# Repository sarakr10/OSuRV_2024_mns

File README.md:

# OSuRV_2024

[Prj table](https://docs.google.com/spreadsheets/d/11ApFMVwyrgWKrQ-Bx30LXNKMNhpXhl4f)

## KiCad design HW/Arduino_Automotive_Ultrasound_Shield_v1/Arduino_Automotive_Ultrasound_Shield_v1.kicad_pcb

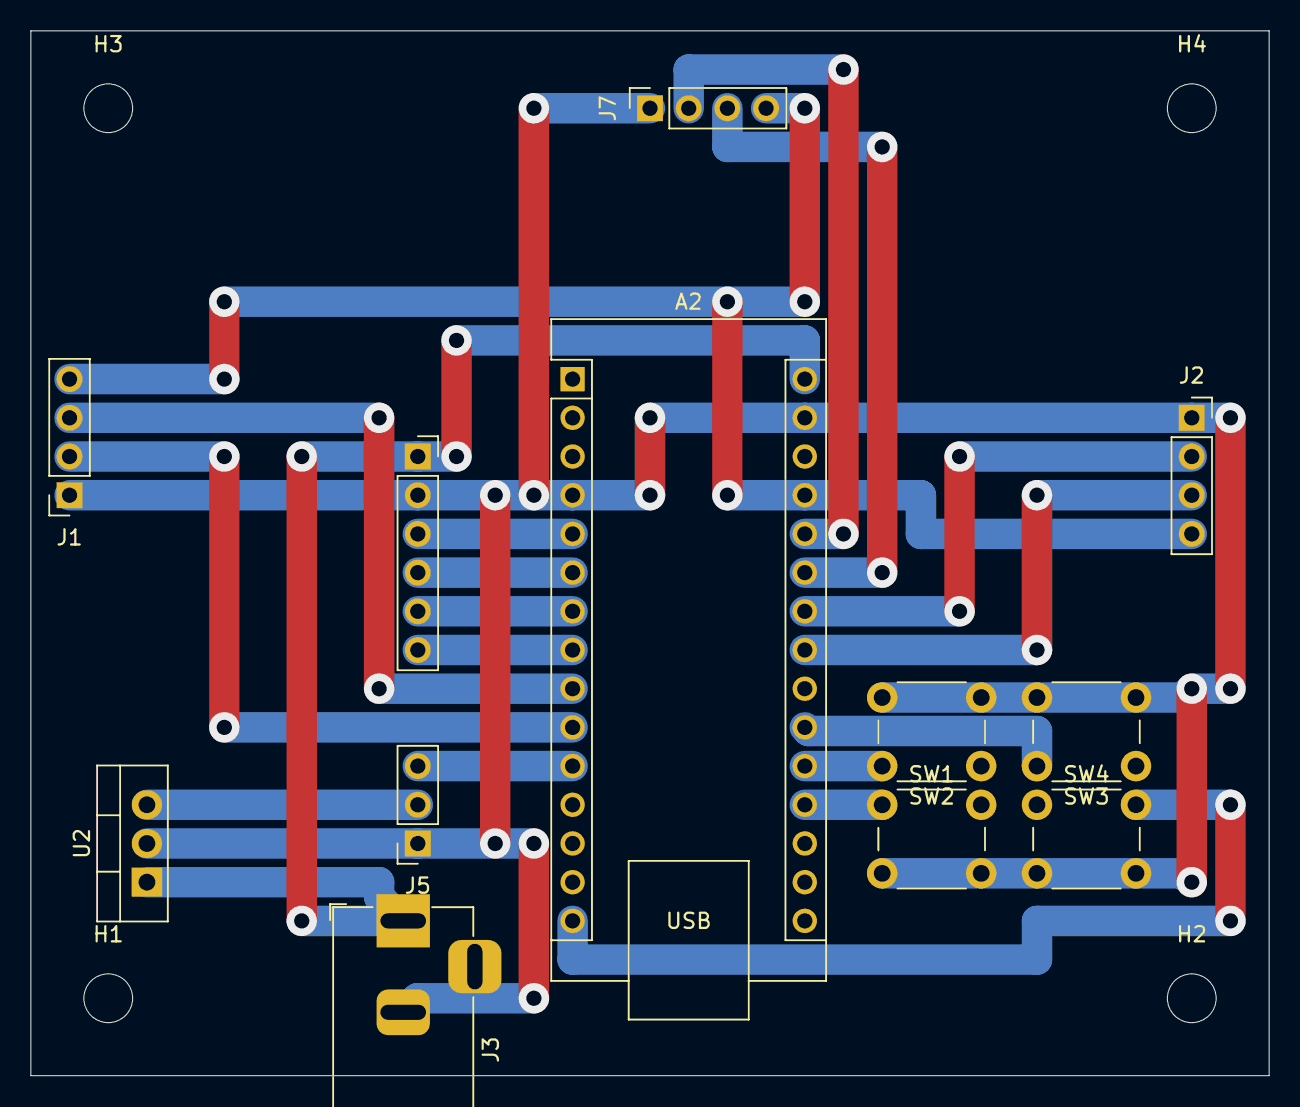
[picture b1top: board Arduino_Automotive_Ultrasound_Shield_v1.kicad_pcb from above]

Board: 2 copper layers, 81.3 x 68.6 mm, 16 parts (0 on the bottom side), 19 nets.

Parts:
A2: Arduino_Nano_Every; Arduino_Nano
H1, H2, H3, H4: M3; MountingHole_3.2mm_M3
J1, J2, J7: 1x4 2.54mm female; PinSocket_1x04_P2.54mm_Vertical
J3: Barrel_Jack_Switch; BarrelJack_Horizontal
J5: 1x3 2.54mm male; PinSocket_1x03_P2.54mm_Vertical
J6: 1x3 2.54mm male; PinSocket_1x06_P2.54mm_Vertical
SW1, SW2, SW3, SW4: SW_Push; SW_PUSH_6mm
U2: LM7805_TO220; TO-220-3_Vertical

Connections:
+5V: A2.27 (+5V), J1.4, J2.4, J7.4
+12V: A2.30 (VIN), J3.1, J6.1, U2.1 (VI)
/BREAK: A2.8 (D5), J6.6
/DIR: A2.7 (D4), J6.5
/ECHO_0: A2.26 (A7), J7.2
/ECHO_1: A2.24 (SCL/A5), J2.2
/ECHO_2: A2.10 (D7), J1.2
/FG: A2.5 (D2), J6.3
/PB0: A2.21 (A2), SW1.1
/PB1: A2.20 (A1), SW2.1
/PB2: A2.19 (A0), SW3.1
/PB3: A2.15 (MISO), SW4.1
/PWM: A2.6 (D3), J6.4
/STEER_PWM: A2.11 (D8), J5.3
/TRIG_0: A2.25 (A6), J7.3
/TRIG_1: A2.23 (SDA/A4), J2.3
/TRIG_2: A2.9 (D6), J1.3
GND: A2.4 (GND), A2.29 (GND), J1.1, J2.1, J3.2, J3.3, J5.1, J6.2, J7.1, SW1.2, SW2.2, SW3.2, SW4.2, U2.2 (GND)
Vdrive: J5.2, U2.3 (VO)

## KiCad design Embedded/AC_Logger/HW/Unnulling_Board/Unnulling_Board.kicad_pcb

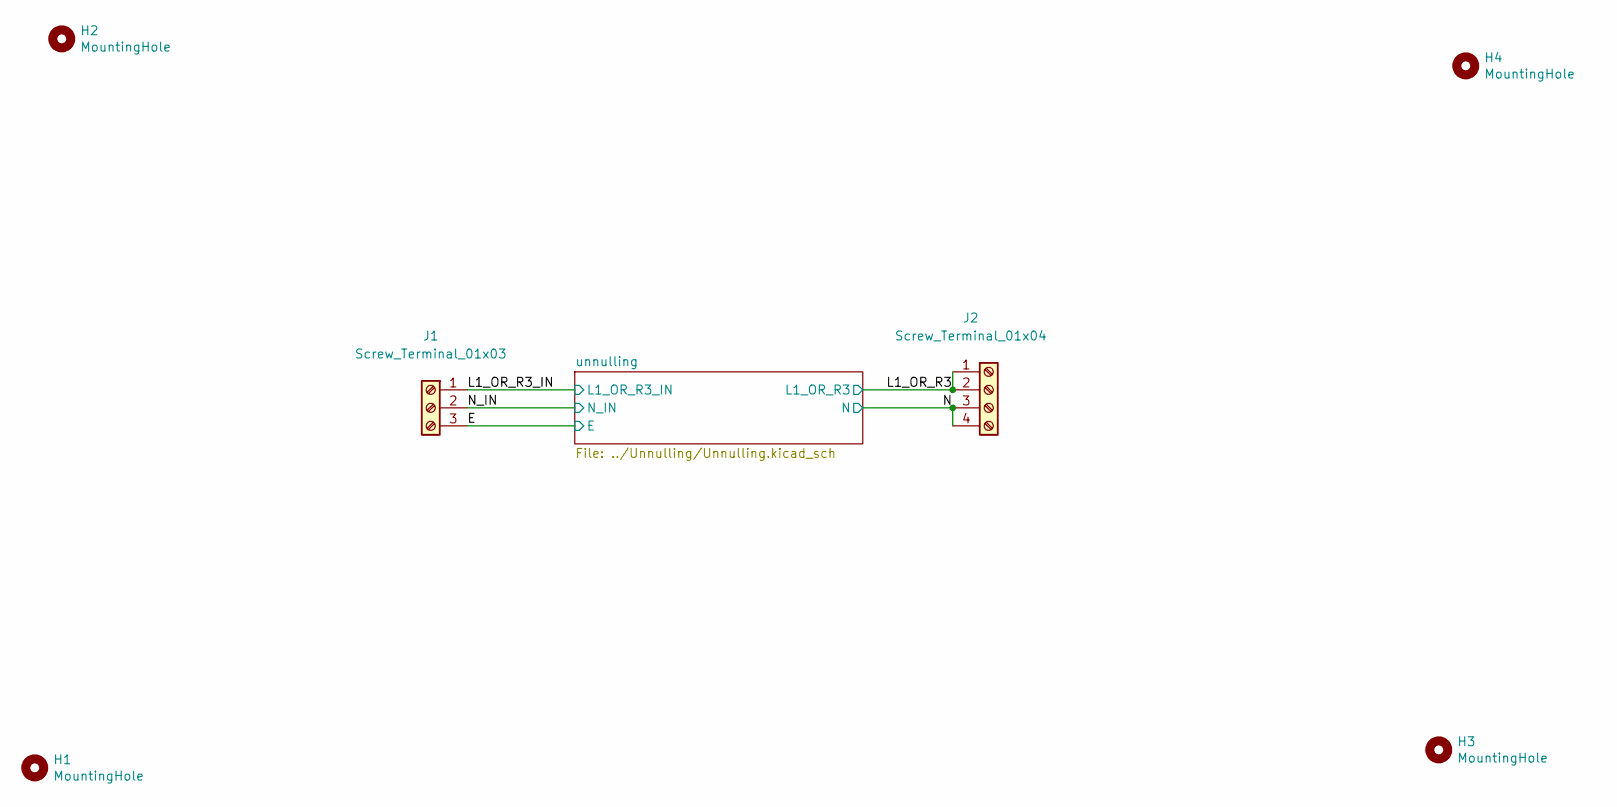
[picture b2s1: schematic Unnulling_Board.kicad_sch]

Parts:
H1, H2, H3, H4: MountingHole; MountingHole_3.2mm_M3_ISO7380_Pad
J1: Screw_Terminal_01x03; TerminalBlock_bornier-3_P5.08mm
J2: Screw_Terminal_01x04; TerminalBlock_bornier-4_P5.08mm

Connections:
/E: J1.3; also elsewhere on the board
/L1_OR_R3: J2.1, J2.2; also elsewhere on the board
/L1_OR_R3_IN: J1.1; also elsewhere on the board
/N: J2.3, J2.4; also elsewhere on the board
/N_IN: J1.2; also elsewhere on the board

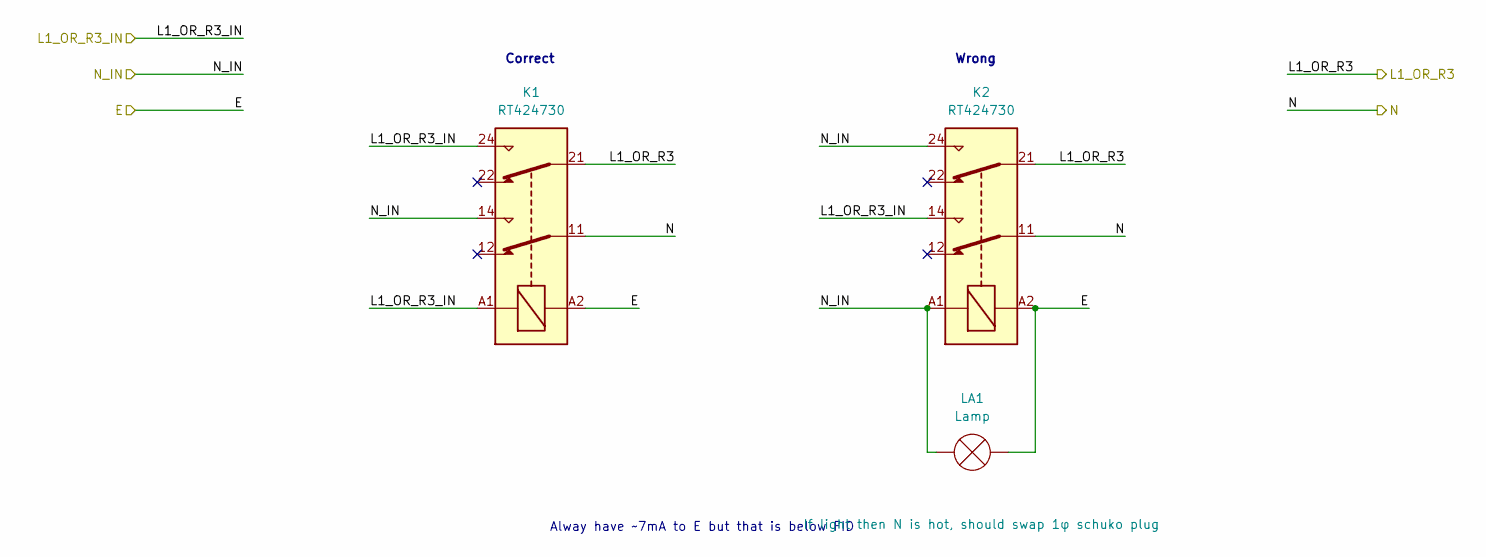
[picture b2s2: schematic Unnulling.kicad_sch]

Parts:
K1, K2: RT424730; Relay_DPDT_Schrack-RT2-FormC_RM5mm
LA1: Lamp; R_Axial_DIN0207_L6.3mm_D2.5mm_P5.08mm_Vertical

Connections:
/E: K1.A2, K2.A2, LA1.1 (-); also elsewhere on the board
/L1_OR_R3: K1.21, K2.21; also elsewhere on the board
/L1_OR_R3_IN: K1.24, K1.A1, K2.14; also elsewhere on the board
/N: K1.11, K2.11; also elsewhere on the board
/N_IN: K1.14, K2.24, K2.A1, LA1.2 (+); also elsewhere on the board

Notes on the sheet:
Alway have ~7mA to E but that is below FID
Wrong
Correct

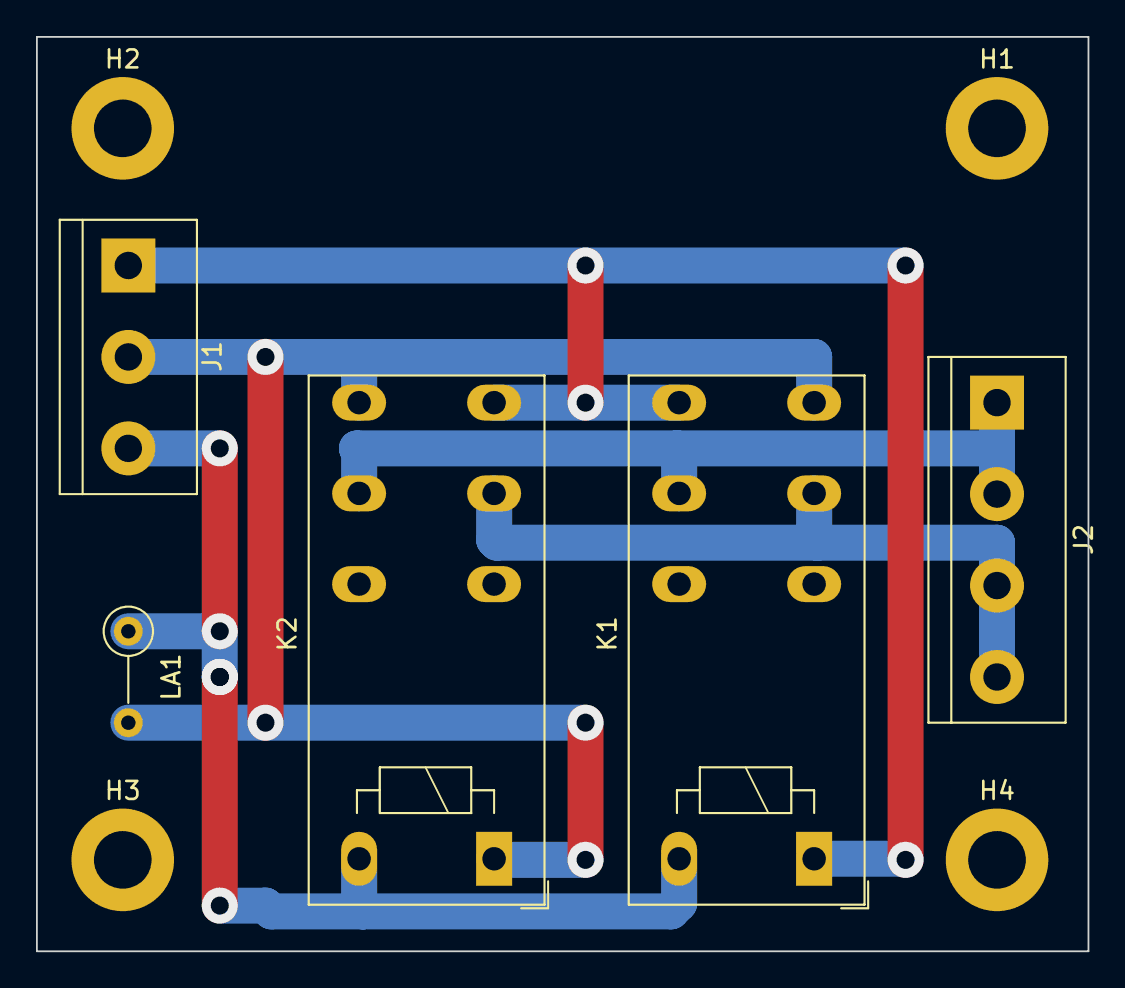
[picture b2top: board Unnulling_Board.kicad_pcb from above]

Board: 2 copper layers, 58.4 x 50.8 mm, 9 parts (0 on the bottom side), 5 nets.

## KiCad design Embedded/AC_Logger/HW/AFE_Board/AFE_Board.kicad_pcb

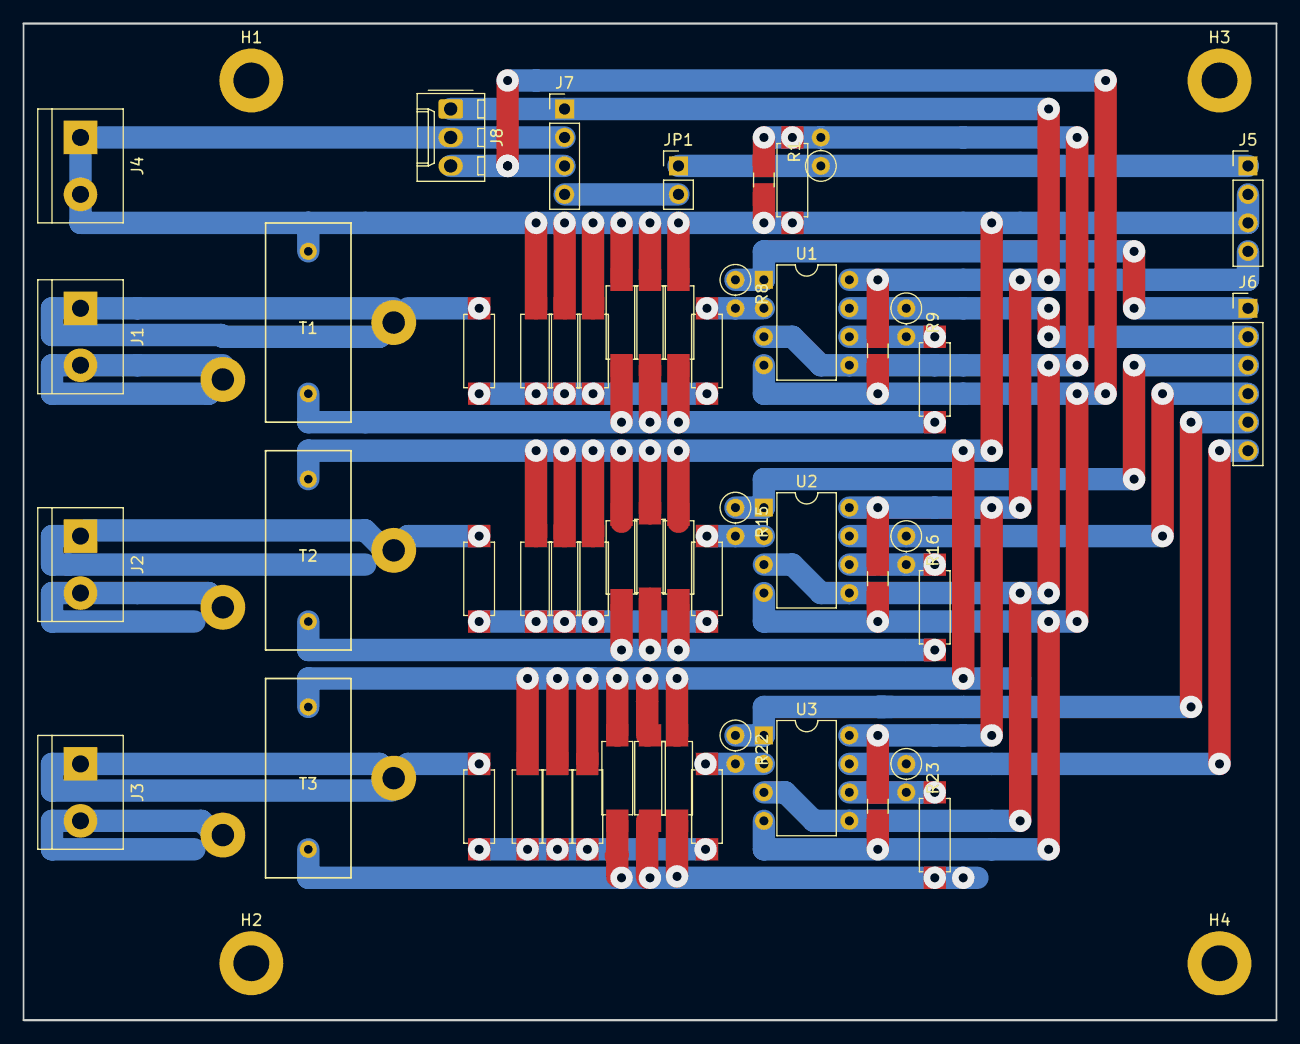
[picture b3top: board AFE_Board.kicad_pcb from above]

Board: 2 copper layers, 111.8 x 88.9 mm, 58 parts (0 on the bottom side), 30 nets.

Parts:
C1, C2, C3, C4: 100n; C_Disc_D3.0mm_W1.6mm_Pinf
D1, D2, D3, D4, D5, D6, D7, D8, D9, D10, D11, D12: 1N4148; R_Axial_DIN0207_L6.3mm_D2.5mm_Pinf_Horizontal
H1, H2, H3, H4: MountingHole; MountingHole_3.2mm_M3_ISO7380_Pad
J1, J2, J3, J4: Screw_Terminal_01x02; TerminalBlock_bornier-2_P5.08mm
J5, J7: Conn_01x04; PinHeader_1x04_P2.54mm_Vertical
J6: Conn_01x06; PinHeader_1x06_P2.54mm_Vertical
J8: NS25-W3P male; Molex_KK-254_AE-6410-03A_1x03_P2.54mm_Vertical
JP1: Jumper_2_Open; PinHeader_1x02_P2.54mm_Vertical
R1: 5k6; R_Axial_DIN0207_L6.3mm_D2.5mm_P2.54mm_Vertical
R2, R5, R12, R19: 1k; R_Axial_DIN0207_L6.3mm_D2.5mm_Pinf_Horizontal
R3, R10, R17: 50; R_Axial_DIN0207_L6.3mm_D2.5mm_Pinf_Horizontal
R4, R11, R18: 1M5; R_Axial_DIN0207_L6.3mm_D2.5mm_Pinf_Horizontal
R6, R7, R13, R14, R20, R21: 100k; R_Axial_DIN0207_L6.3mm_D2.5mm_Pinf_Horizontal
R8, R9, R15, R16, R22, R23: 220k; R_Axial_DIN0207_L6.3mm_D2.5mm_P2.54mm_Vertical
T1, T2, T3: ASM-010
U1, U2, U3: TL072; DIP-8_W7.62mm

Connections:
/A0: J6.1, R8.1, U1.1
/A1: J6.2, R9.1, U1.7
/A2: J6.3, R15.1, U2.1
/A3: J6.4, R16.1, U2.7
/A4: J6.5, R22.1, U3.1
/A5: J6.6, R23.1, U3.7
/AFE/sensor0/amp0/I_IN: D2.1 (K), D4.2 (A), R3.1, R6.2, T1.1 (AA)
/AFE/sensor0/amp0/V_IN: D1.1 (K), D3.2 (A), R4.2, R5.1, R7.2
/AFE/sensor1/amp0/I_IN: D6.1 (K), D8.2 (A), R10.1, R13.2, T2.1 (AA)
/AFE/sensor1/amp0/V_IN: D5.1 (K), D7.2 (A), R11.2, R12.1, R14.2
/AFE/sensor2/amp0/I_IN: D10.1 (K), D12.2 (A), R17.1, R20.2, T3.1 (AA)
/AFE/sensor2/amp0/V_IN: D9.1 (K), D11.2 (A), R18.2, R19.1, R21.2
/E1_OR_S3_IN: J2.2, T2.3 (SA)
/E1_OR_S3_OUT: J2.1, R11.1, T2.4 (SB)
/L1_OR_R3_IN: J1.2, T1.3 (SA)
/L1_OR_R3_OUT: J1.1, R4.1, T1.4 (SB)
/T3_IN: J3.2, T3.3 (SA)
/T3_OUT: J3.1, R18.1, T3.4 (SB)
GND: C1.2, D1.2 (A), D2.2 (A), D3.1 (K), D4.1 (K), D5.2 (A), D6.2 (A), D7.1 (K), D8.1 (K), D9.2 (A), D10.2 (A), D11.1 (K), D12.1 (K), J4.1, J4.2, J5.2, J5.3, J7.2, J8.2, R2.2, R3.2, R5.2, R10.2, R12.2, R17.2, R19.2, T1.2 (AB), T2.2 (AB), T3.2 (AB)
unnamed: J7.4, JP1.2 (B)
unnamed: R6.1, R9.2, U1.6 (-)
unnamed: R7.1, R8.2, U1.2 (-)
unnamed: R13.1, R16.2, U2.6 (-)
unnamed: R14.1, R15.2, U2.2 (-)
unnamed: R20.1, R23.2, U3.6 (-)
unnamed: R21.1, R22.2, U3.2 (-)
VCC: C2.1, C3.1, C4.1, J5.4, J7.1, J8.1, U1.8 (V+), U2.8 (V+), U3.8 (V+)
VDD: J5.1, JP1.1 (A), R1.1
VDDF: C1.1, R1.2, R2.1, U1.3 (+), U1.5 (+), U2.3 (+), U2.5 (+), U3.3 (+), U3.5 (+)
VEE: C2.2, C3.2, C4.2, J7.3, J8.3, U1.4 (V-), U2.4 (V-), U3.4 (V-)

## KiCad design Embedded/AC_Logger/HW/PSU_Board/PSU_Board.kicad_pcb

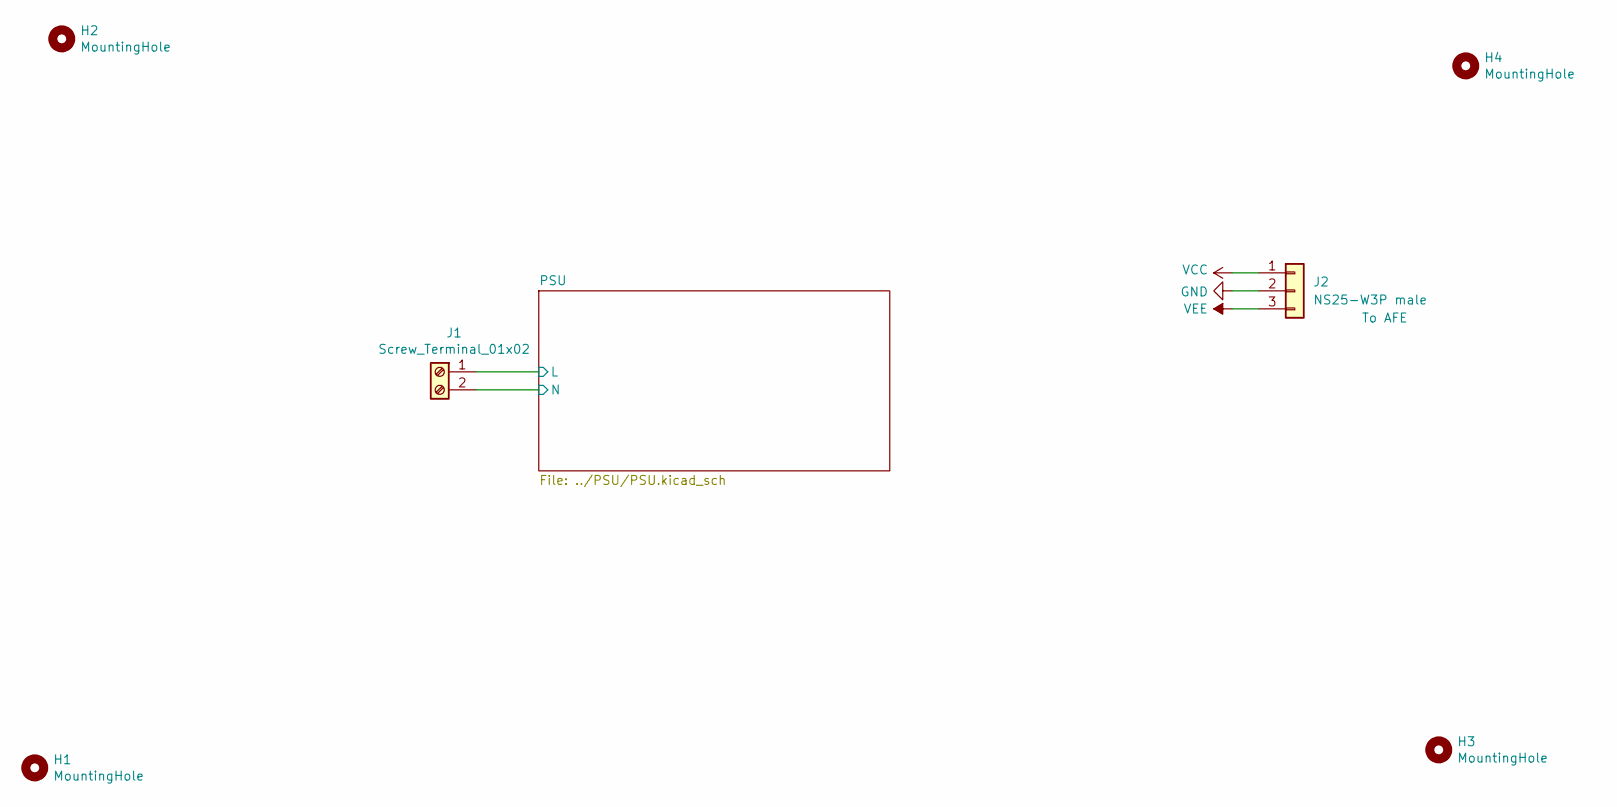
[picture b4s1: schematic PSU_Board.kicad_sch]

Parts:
H1, H2, H3, H4: MountingHole; MountingHole_3.2mm_M3_ISO7380_Pad
J1: Screw_Terminal_01x02; TerminalBlock_bornier-2_P5.08mm
J2: NS25-W3P male; Molex_KK-254_AE-6410-03A_1x03_P2.54mm_Vertical

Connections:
/PSU/L: J1.1; also elsewhere on the board
/PSU/N: J1.2; also elsewhere on the board
GND: J2.2; also elsewhere on the board
VCC: J2.1; also elsewhere on the board
VEE: J2.3; also elsewhere on the board

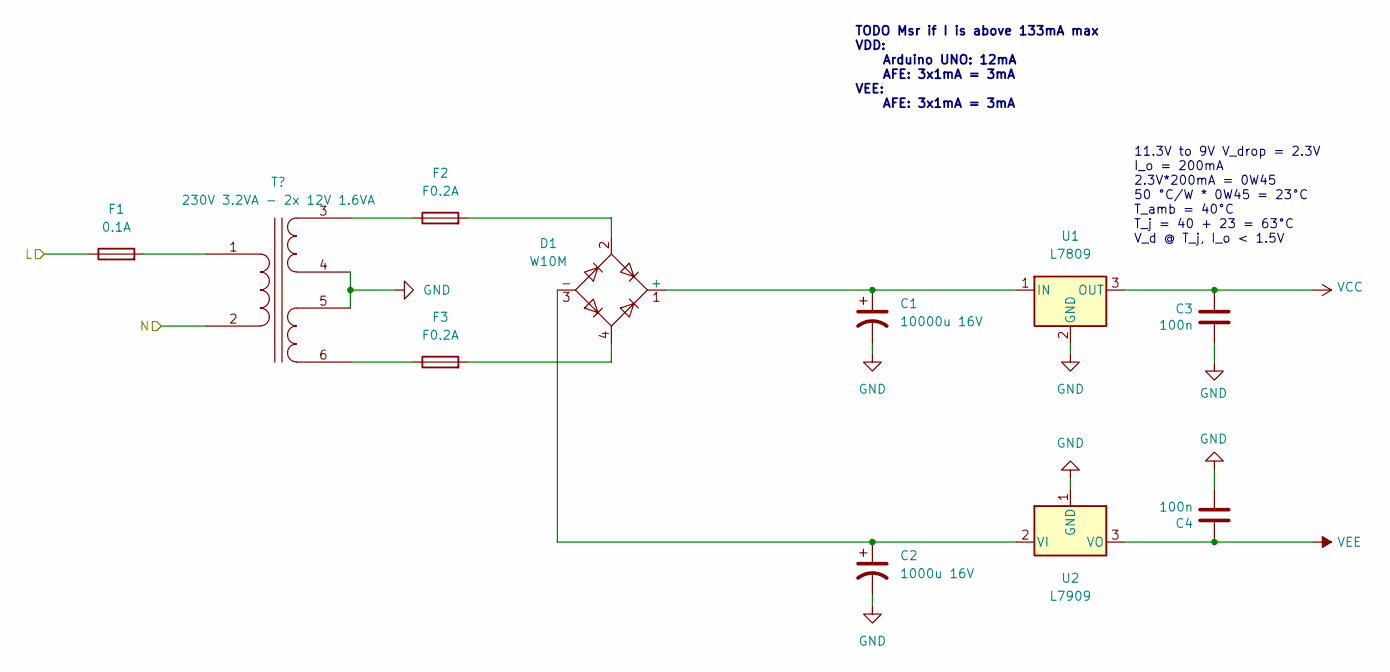
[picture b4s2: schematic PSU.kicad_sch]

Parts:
C1: 10000u 16V; CP_Radial_D16.0mm_P7.50mm
C2: 1000u 16V; CP_Radial_D10.0mm_P5.00mm
C3, C4: 100n; C_Disc_D3.0mm_W1.6mm_P2.50mm
D1: W10M; Diode_Bridge_Round_D9.8mm
F1: 0.1A; Fuseholder_Clip-5x20mm_Littelfuse_111_Inline_P20.00x5.00mm_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
F2, F3: F0.2A; Fuseholder_Clip-5x20mm_Littelfuse_111_Inline_P20.00x5.00mm_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
U1: L7809; TO-220-3_Vertical
U2: L7909; TO-220-3_Vertical

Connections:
/PSU/L: F1.1; also elsewhere on the board
GND: C1.2, C2.2, C3.2, C4.2, U1.2 (GND), U2.1 (GND); also elsewhere on the board
unnamed: C1.1, D1.1 (+), U1.1 (IN)
unnamed: C2.1, D1.3 (-), U2.2 (VI)
unnamed: D1.2, F2.2
unnamed: D1.4, F3.2
unnamed 7: F1.2; also elsewhere on the board
unnamed 8: F2.1; also elsewhere on the board
unnamed 9: F3.1; also elsewhere on the board
VCC: C3.1, U1.3 (OUT); also elsewhere on the board
VEE: C4.1, U2.3 (VO); also elsewhere on the board

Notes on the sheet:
TODO Msr if I is above 133mA max VDD: Arduino UNO: 12mA AFE: 3x1mA = 3mA VEE: AFE: 3x1mA = 3mA
11.3V to 9V V_drop = 2.3V I_o = 200mA 2.3V*200mA = 0W45 50 °C/W * 0W45 = 23°C T_amb = 40°C T_j = 40 + 23 = 63°C V_d @ T_j, I_o < 1.5V

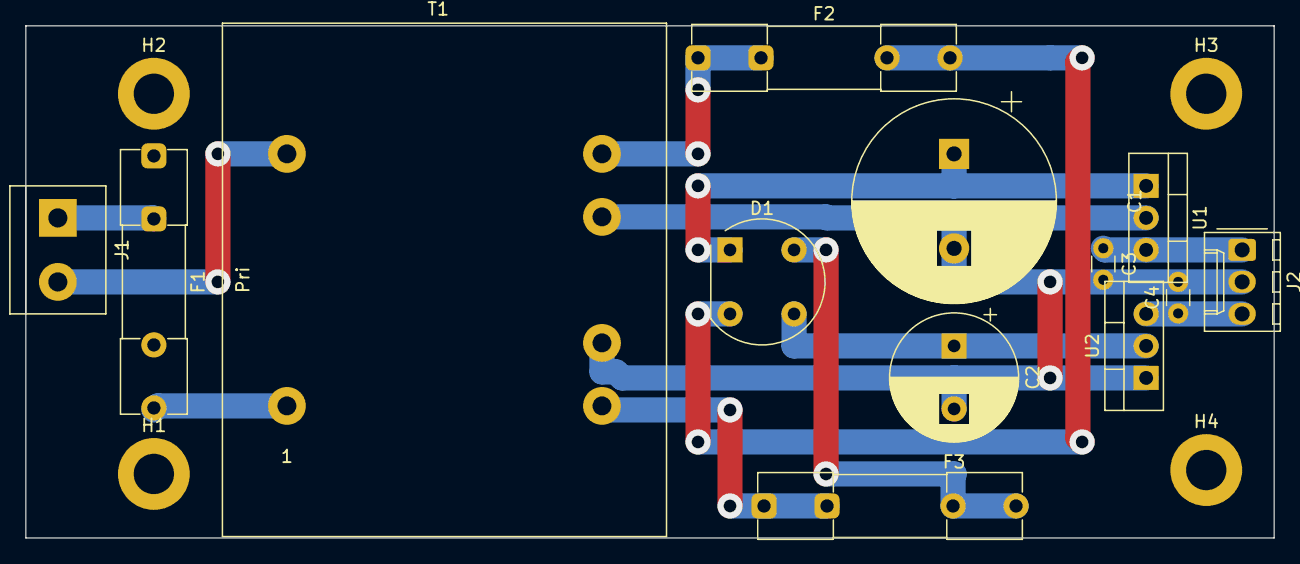
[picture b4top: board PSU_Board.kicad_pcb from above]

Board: 2 copper layers, 99.1 x 40.6 mm, 17 parts (0 on the bottom side), 12 nets.

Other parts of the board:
T1: 230V 3.2VA - 2x 12V 1.6VA; Transformer-3VA_2xSec

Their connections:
/PSU/N: T1.2 (AB); also elsewhere on the board
GND: T1.4 (SB), T1.5 (SC); also elsewhere on the board
unnamed 7: T1.1 (AA); also elsewhere on the board
unnamed 8: T1.3 (SA); also elsewhere on the board
unnamed 9: T1.6 (SD); also elsewhere on the board

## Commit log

2024-11-29 Adding old stuff.
2024-11-29 Merging what LPRS_2024 crew done.
2024-11-29 Corrected name.
2024-11-29 Updated to new KiCAD version.
2025-06-05 N64 resources.
2025-06-09 Code for tank.
2025-06-09 BLDC test.
2025-06-10 Servo motor
2025-06-11 senzor
2025-06-11 sa senzorom
2025-06-12 ploca
2025-06-17 kompletno
2025-06-19 promenjen pin
2025-07-08 test
2025-07-09 objasnjenja
2025-07-09 dokumentacija
